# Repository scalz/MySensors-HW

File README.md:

# Mysensors HW
My personal Workspace for MySensors Hardware

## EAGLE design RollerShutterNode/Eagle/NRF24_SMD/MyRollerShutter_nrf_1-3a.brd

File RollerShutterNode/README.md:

# MyRollerShutter

This is a board for controlling rollershutters (0-100%) and detecting end stops with ACS712 for current sense of motor. 
It can control 3-wire motor only (Power, Up, Down wires), DC or AC, 12 to 230V. It's fine for me as I'm using AC motor. But this board can't work with 2wire DC motor.
You can connect 3 push buttons (UP/DOWN/STOP) and/or external i2c device (for tactile, gesture...). 

Of course, it can also be used as a relay board.

It is derived in two versions :

- NRF24 smd
- RFM69CW

I am using it with Mysensors lib. It's fun :)

### Important Note : I share this work for educational purpose. Be very careful with this. It's an AC Board which can be lethal. If you don't know what you are doing, I can't tell you enough to not do anything. 

### General 
------

|General spec.|  | 
|---|---|
|Size |44.4*45.4 (mm) |
| Components size | 0805 |
| MCU | Atmel328p TQFP |
| Radio | two versions : NRF24 smd or RFM69CW |
| Authentication security | ATSHA204A chip footprint |
| OverTheAir update | SPI flash eeprom footprint |
| Current Sensor | ACS712 5Amp current flow sensors footprint with  opamp signal condition. to have a nice 0-3V ADC curve |
| Relays | 2x 10Amp relays : OMRON G5Q type, 1xNO, 1xNO-NC for their footprint and quality|
| AC/DC Stepdown | HILINK_HLK-PM01 230V->5V |
| Screw terminals | 5mm pitch. Input AC, Motor Power Source, Motor Direction|
| Extension connectors | 3x JST 1mm pitch connectors : FTDI, AVRSPI, IOs | 

#### Onboard safety:

- Varistor 
- 5Amp fuse on AC Mains Input to handle relays. 
- 1Amp fuse for Hilink AC/DC Stepdown. 
- DS18B20A sensor for monitoring AC/DC step down temperature. 
- A dual relay driver to handle relays and parasite. 
- Milling slots for additional creepage.
- you can also : put some liquid tape on your AC pcb pads, and use an insulating box.

#### Extension Connectors description

- FTDI : JST 1mm pitch connector
- AVRSPI : JST 1mm pitch connector
- IOs : JST 1mm pitch connector -> 3V/GND/A4/A5/D3, for UP/DOWN/STOP buttons or I2C for external breakout (tactile switch, gesture...) or some shields I have designed :)

#### AC Connectors description
|Connector|  |
|---|---|
| Input AC | connect to AC line L to Live and N to Neutral |
| MotorPowerSource | for 12-24VDC just connect power source to 12_230 screwterminal, for 110-230V connect together the pins from Motor Power screwterminal |
|Motor Direction | Motor Up and Down lines |

#### Arduino Pin description
|Arduino sketch define| Arduino Pin | description |
|---|---|---|
| MY_OTA_FLASH_SS | 8 | EEprom CS pin |
| ATSHA204_PIN | 17/A3 | Arduino Digital I/O pin number for ATSHA204A sot23 ic (for authentication) |
| RELAY_UPDOWN  | 15/A1 | Digital I/O pin number for relay SPDT |
| RELAY_POWER | 16/A2 | Digital I/O pin number for relay SPST : Normally open, power off rollershutter motor, if A2==1 and A1==0 moveup, if A2==1 and A1==1 movedown, if A2==0 power off |
| DEBUG_LED |  6 | Digital I/O pin number for onboard debug led |
| BUTTON_STOP | 3 | Digital I/O pin number for button Stop |
| BUTTON_UP | 18/A4 | Digital I/O pin number for button Up or I2C |
| BUTTON_DOWN | 19/A5  | Digital I/O pin number for button Down or I2C |
| ACS712_SENSOR | A7 | ADC pin for ACS712 current sensor |
| DS18B20_PIN | 4 | One Wire Temperature sensor for onboard monitoring |

#### Q&A about my personal choice
##### Why not an ESP?
- I like these chips. But I don't want wifi for my rollershutter nodes. I prefer to use subghz radio+atsha signing ic.

##### Why current sensor for endstop detection?
- There are other option for just detecting a simple trigger, sure. I looked at it briefly, there was not a so big footprint saving, and I thought the current sensor would add more verstality to the board.

##### Why so much capa, using filtering for analog etc..
- some ferrites, caps etc. are not all mandatory. they help to improve things but without some parts it works well. It's there, in case, for debug, and still useful when there are some footprints available.

etc..

Finally :

- as each new thing I make, I enjoy the new challenge.
- I have tried to make a board dedicated for RollershutterNode with autocalibration, with as much features/options/versatility I could with the available footprint. 

#### About the ACS current sensor

ACS reading measurement results, from 0 to 1000W by 100W step :

For fun, this is the light bulbs I have used to do my measurements (5 lights bulbs can be powered separately, the other row in one time, so it's possible to do 100W steps)

For detail about opamp circuit see schematic.

### Example of use of this board : RollershutterNode 

#### How is the Rollershutter motor controlled:

On-board, there are 2x10Amp Relays. Rollershutter motor don't use 10Amp of course, nor 5Amp. May we expect no need of snubber, if using over rated relays? I hope :) If mandatory for you then, it should be external, not enough space onboard. That said, for a simple relay board too, you can control lot of thing with 10amp.

So, we have 2 relays, for the rollershutter:

- 1x NO  which enable/disable power on the second relay. It is like "Stop Motor".
- 1X NO-NC that you can toggle, and drive Up, or Down the rollershutter motor. Remember this relay needs to be enabled by the previous one.
    So relays are "interlocked", you can't enable "Up" and "Down" outputs to motor at same time and burn your motor.

#### How to open/close 0-100%

We need to detect the up and down endstops. It is managed by the onboard ACS7125 sensor. It will senses the motor current flow and we will read it with ADC on arduino. 
When motor is active, there is a power consumption. And when an up or down end is toggled, the motor stops (because of mechanical switch...). There is no power consumption. 

As you can see, with ACS712, we can know in which state we are. We are able to read some kind of power consuption curve too if needed and no mechanical ends switch available..
So, we need to know how long it takes to open the rollershutter, and to close (it may be not the exact timing open vs close time). 

#### Example sketch 

Note: the example sketch is for Mysensors v2.x. You can find it in example folder. It is state machine based, so no blocking loop. It's not very polished but it's working. I miss time, too much ideas&projects..I will look at it later. 

1. You just need to config your settings in the MyNodeDefinition.h
2. The ShutterSM.h and .cpp are the state machine for the shutter. You don't need to modify it, there are default settings.
3. State and settings of rollershutter are stored in eeprom.

The sketch present the following Mysensors CHILD_IDs, presented to a controller for instance :

| CHILD_ID | Description | 
|---|---|
| CHILD_ID_ROLLERSHUTTER | handle UP/DOWN/STOP/PERCENT |
| CHILD_ID_AUTOCALIBRATION | remotely start a calibration |
| CHILD_ID_TEMPERATURE | onboard temperature sensor, to monitor board&Hilink temperature |
| CHILD_ID_ENDSTOP | endstop. for debugging in case...Set it to simulate an endstop during calibration and tell the node that the shutter has reached the endstop (in case no mechanical switch etc..) |
| CHILD_ID_PERCENT | Rollershutter PERCENT for controller which are not Mysensors 2.0 compliant yet |
| CHILD_ID_CURRENT |Current sensor value, for debugging.. |

**At first launch**, the node will use the default values in the state machine and will know it's not calibrated. So, you can launch a calibration. That will automatically :

1. fully open the shutter.
2. fully close it and measure travel time.
3. fully open it and measure the travel time.
4. Done. Yeah! Parameters are stored in eeprom. 
5. If you push Up button, that will try to fully open. Down, Stop buttons will do their job too. The node store the new position in eeprom. From your controller, set a PERCENT and that will open as you want your shutter. so fun, so cool :)
etc..

### Overview

&nbsp; 

### Notes : 

### TODO

- 3d insulating case
- improve things. always improve :)

### Donations

I'm trying to make opensource projects. I do this for free and sharing spirit. I don't do ads etc..
But if you think information here is worth of some money, or want to reward me, feel free to send any amount through paypal.

Or you can also order pcb here :
I will earn a little percentage that will allow me to order proto pcb and share more fun design.

Or pay me a protein smoothie if you see me! oh well, a beer is ok too :)

### Contributors

Special thanks to:
- Mysensors Team for its great work
- Adafruit, sparkfun, TI, atmel etc.. for all educational infos they share

### Links, reference and license 

https://www.openhardware.io/view/22/Roller-Shutter-Node

Copyright Scalz (2016). released under the [CERN Open Hardware Licence v1.2](http://ohwr.org/cernohl)

This is an opensource hardware. So please respect at least license and do what you want with it ;)

Enjoy :)

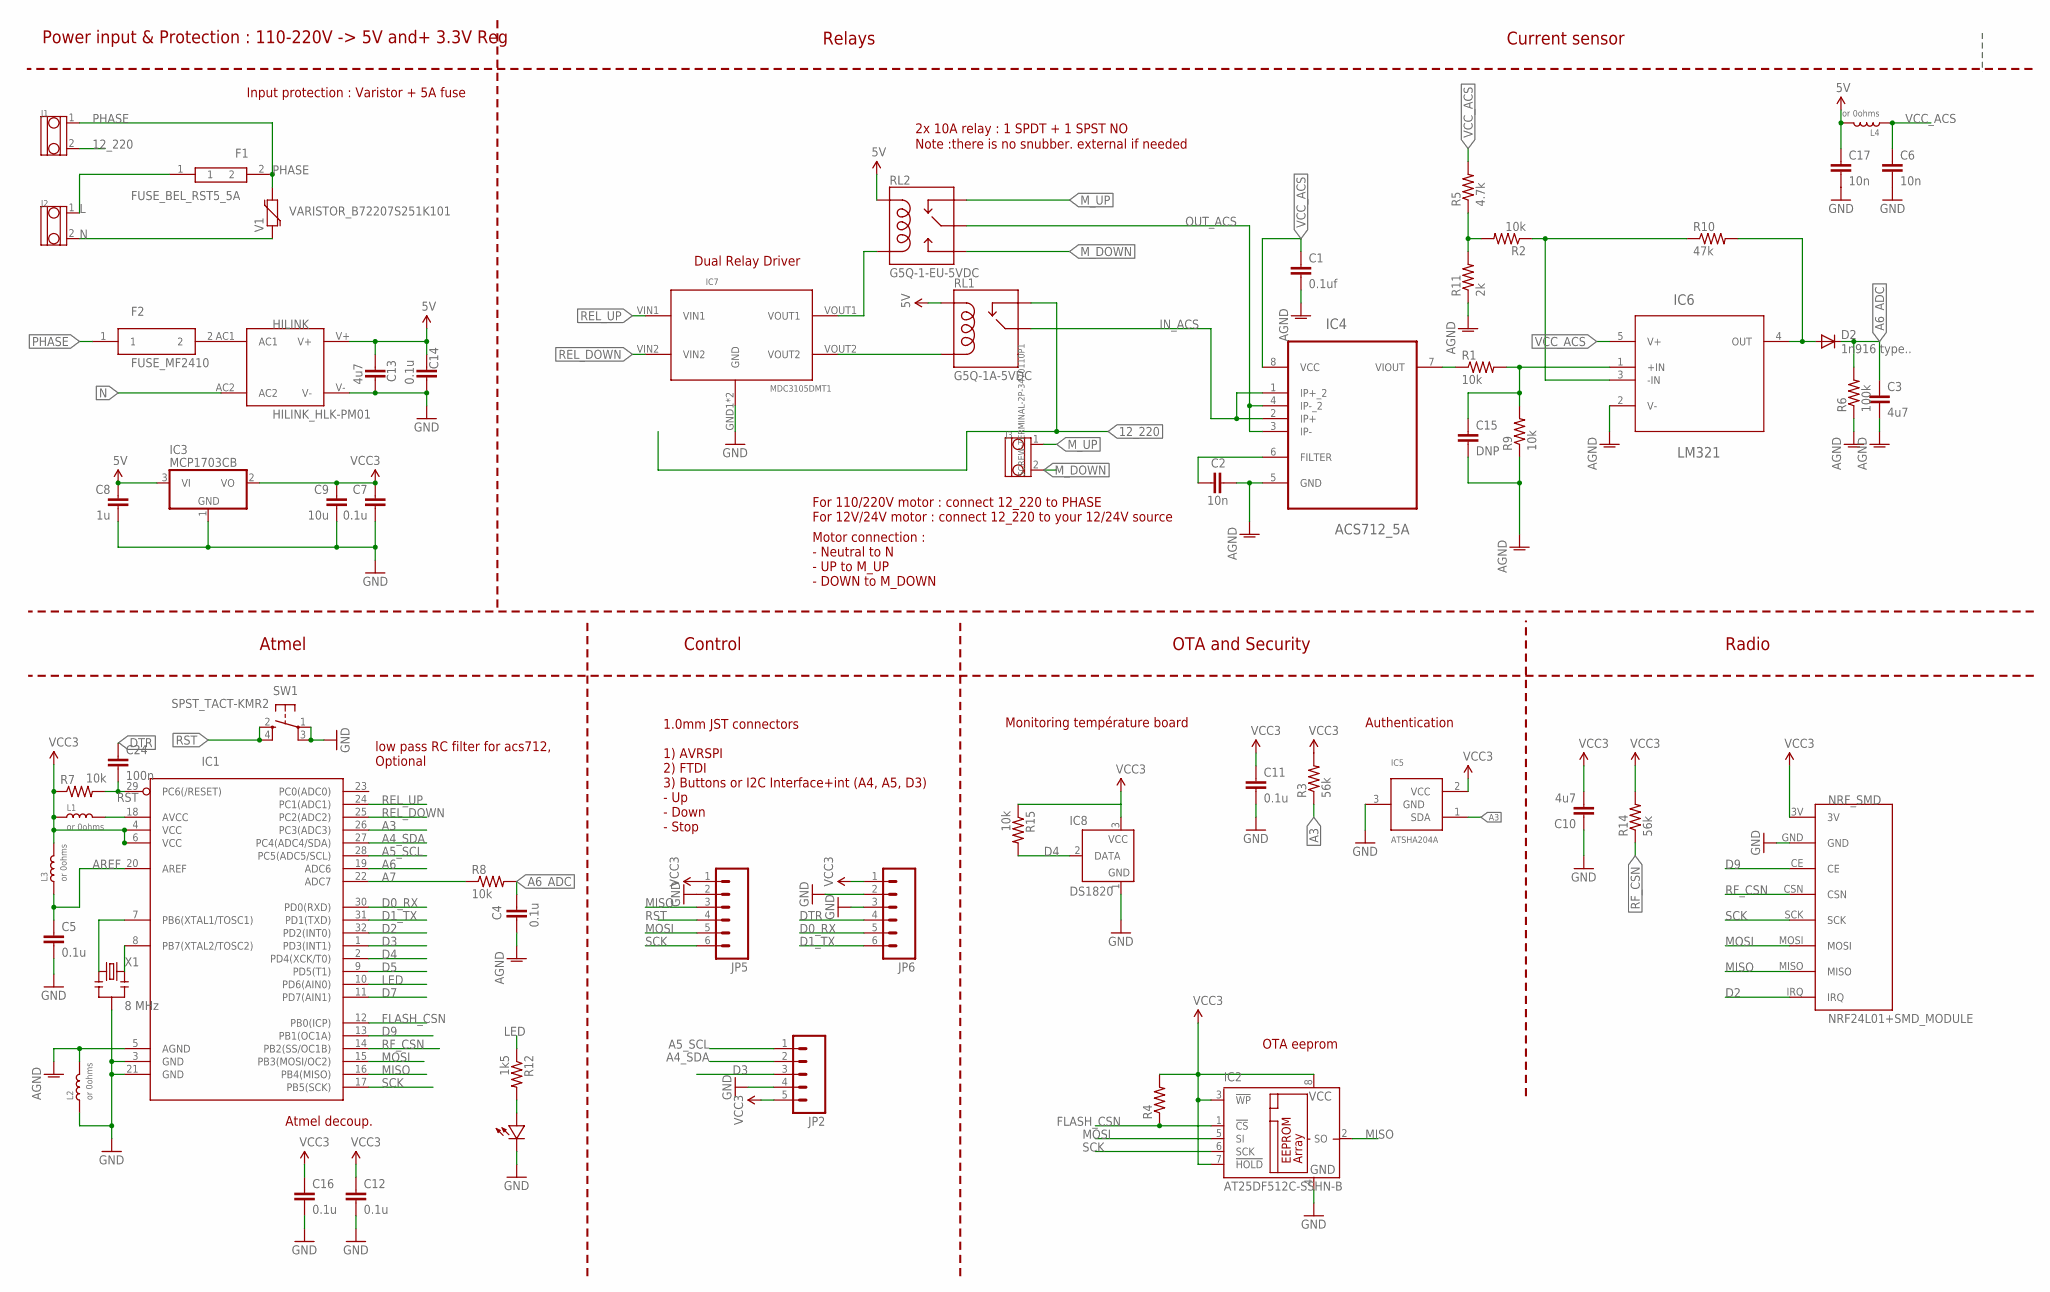
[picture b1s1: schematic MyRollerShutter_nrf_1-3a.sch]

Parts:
C1: 0.1uf; 0805-CAP
C2, C6, C17: 10n; 0805-CAP
C3, C10, C13: 4u7; 0805-CAP
C4, C5, C7, C11, C12, C14, C16: 0.1u; 0805-CAP
C8: 1u; 0805-CAP
C9: 10u; 0805-CAP
C15: DNP; 0805-CAP
C24: 100n; 0805-CAP
D1: LED0805; 0805-LED
D2: 1n916 type..; SOD-323
F1: FUSE_BEL_RST5_5A
F2: FUSE_MF2410; 2410
HILINK: HILINK_HLK-PM01
IC1: ATMega-328; TQFP32-08
IC2: AT25DF512C-SSHN-B; SO-08
IC3: MCP1703CB; SOT23
IC4: ACS712_5A; SOIC127P600X175-8N
IC5: ATSHA204A; SOT23
IC6: LM321; SOT95P285X120-5N
IC7: MDC3105DMT1
IC8: DS1820; TO92-
J1, J2, J3: SCREW-TERMINAL-2P-3470110P1; 2P-5.0
JP2: M05SMD; 1X05-1MM
JP5, JP6: M06SMD-1MM; 1X06-1MM
L1, L2, L3, L4: or 0ohms; L0805
NRF_SMD: NRF24L01+SMD_MODULE
R1, R2, R7, R8, R9, R15: 10k; 0805-RES
R3, R14: 56k; 0805-RES
R4: RESISTOR0805-RES; 0805-RES
R5: 4.7k; 0805-RES
R6: 100k; 0805-RES
R10: 47k; 0805-RES
R11: 2k; 0805-RES
R12: 1k5; 0805-RES
RL1: G5Q-1A-5VDC; G5Q_SINGLE
RL2: G5Q-1-EU-5VDC; RELAY-G5Q
SW1: SPST_TACT-KMR2; KMR2
V1: VARISTOR_B72207S251K101
X1: 8 MHz; RESONATOR-SMD

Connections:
5V: C8.1, C13.1, C14.1, C17.1, HILINK.V+, IC3.3 (VI), L4.2, RL1.1 (COIL1), RL2.5 (COIL1)
12_220: J1.2, RL1.3 (NC)
A3: IC1.26 (PC3(ADC3)), IC5.1 (SDA), R3.1
A4_SDA: IC1.27 (PC4(ADC4/SDA)), JP2.2
A5_SCL: IC1.28 (PC5(ADC5/SCL)), JP2.1
A6: IC1.19 (ADC6)
A6_ADC: C3.1, C4.2, D2.1 (C), R6.2, R8.2
A7: IC1.22 (ADC7), R8.1
AGND: C1.2, C2.2, C3.2, C4.1, C15.2, IC1.5 (AGND), IC4.5 (GND), IC6.2 (V-), L2.2, R6.1, R9.1, R11.1
AREF: C5.1, IC1.20 (AREF), L3.1
D0_RX: IC1.30 (PD0(RXD)), JP6.5
D1_TX: IC1.31 (PD1(TXD)), JP6.6
D2: IC1.32 (PD2(INT0)), NRF_SMD.IRQ
D3: IC1.1 (PD3(INT1)), JP2.3
D4: IC1.2 (PD4(XCK/T0)), IC8.2 (DATA), R15.2
D5: IC1.9 (PD5(T1))
D7: IC1.11 (PD7(AIN1))
D9: IC1.13 (PB1(OC1A)), NRF_SMD.CE
DTR: C24.1, JP6.4
FLASH_CSN: IC1.12 (PB0(ICP)), IC2.1 (!CS), R4.1
GND: C5.2, C6.2, C7.2, C8.2, C9.2, C10.1, C11.2, C12.2, C13.2, C14.2, C16.2, C17.2, D1.MINUS, HILINK.V-, IC1.3 (GND), IC1.21 (GND), IC2.4 (GND), IC3.1 (GND), IC5.3 (GND), IC7.GND1 (GND), IC7.GND2 (GND), IC8.1 (GND), JP2.4, JP5.2, JP6.2, JP6.3, L2.1, NRF_SMD.GND, SW1.1, SW1.3 (P1), X1.2
IN_ACS: IC4.1 (IP+_2), IC4.2 (IP+), RL1.2 (MAIN)
L: F1.1, J2.1
LED: IC1.10 (PD6(AIN0)), R12.1
LM_OUT: D2.2 (A), IC6.4 (OUT), R10.2
MISO: IC1.16 (PB4(MISO)), IC2.2 (SO), JP5.3, NRF_SMD.MISO
MOSI: IC1.15 (PB3(MOSI/OC2)), IC2.5 (SI), JP5.5, NRF_SMD.MOSI
M_DOWN: J3.2, RL2.3 (NO)
M_UP: J3.1, RL2.4 (NC)
N: HILINK.AC2, J2.2, V1.1
unnamed: C2.1, IC4.6 (FILTER)
unnamed: IC4.7 (VIOUT), R1.1
unnamed: IC1.18 (AVCC), L1.2
unnamed: IC7.VOUT2, RL1.5 (COIL2)
unnamed: F2.2, HILINK.AC1
unnamed: C15.1, IC6.1 (+IN), R1.2, R9.2
unnamed: IC6.3 (-IN), R2.1, R10.1
unnamed: IC1.7 (PB6(XTAL1/TOSC1)), X1.1
unnamed: D1.PLUS, R12.2
unnamed: R2.2, R5.1, R11.2
unnamed: IC7.VOUT1, RL2.1 (COIL2)
unnamed: IC1.8 (PB7(XTAL2/TOSC2)), X1.3
OUT_ACS: IC4.3 (IP-), IC4.4 (IP-_2), RL2.2 (MAIN)
PHASE: F1.2, F2.1, J1.1, V1.2
REL_DOWN: IC1.25 (PC2(ADC2)), IC7.VIN2
REL_UP: IC1.24 (PC1(ADC1)), IC7.VIN1
RF_CSN: IC1.14 (PB2(SS/OC1B)), NRF_SMD.CSN, R14.1
RST: C24.2, IC1.29 (PC6(/RESET)), JP5.4, R7.2, SW1.2 (S), SW1.4 (S1)
SCK: IC1.17 (PB5(SCK)), IC2.6 (SCK), JP5.6, NRF_SMD.SCK
VCC: C7.1, C9.1, C10.2, C11.1, C12.1, C16.1, IC1.4 (VCC), IC1.6 (VCC), IC2.3 (!WP), IC2.7 (!HOLD), IC2.8 (VCC), IC3.2 (VO), IC5.2 (VCC), IC8.3 (VCC), JP2.5, JP5.1, JP6.1, L1.1, L3.2, NRF_SMD.3V, R3.2, R4.2, R7.1, R14.2, R15.1
VCC_ACS: C1.1, C6.1, IC4.8 (VCC), IC6.5 (V+), L4.1, R5.2

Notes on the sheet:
Authentication
Control
1.0mm JST connectors 1) AVRSPI 2) FTDI 3) Buttons or I2C Interface+int (A4, A5, D3) - Up - Down - Stop
Input protection : Varistor + 5A fuse
Dual Relay Driver
Power input & Protection : 110-220V -> 5V and+ 3.3V Reg
Relays
Current sensor
OTA and Security
Radio
Atmel
low pass RC filter for acs712, Optional
Note :there is no snubber. external if needed
Atmel decoup.
2x 10A relay : 1 SPDT + 1 SPST NO
Monitoring température board
For 110/220V motor : connect 12_220 to PHASE For 12V/24V motor : connect 12_220 to your 12/24V source
Motor connection : - Neutral to N - UP to M_UP - DOWN to M_DOWN
OTA eeprom

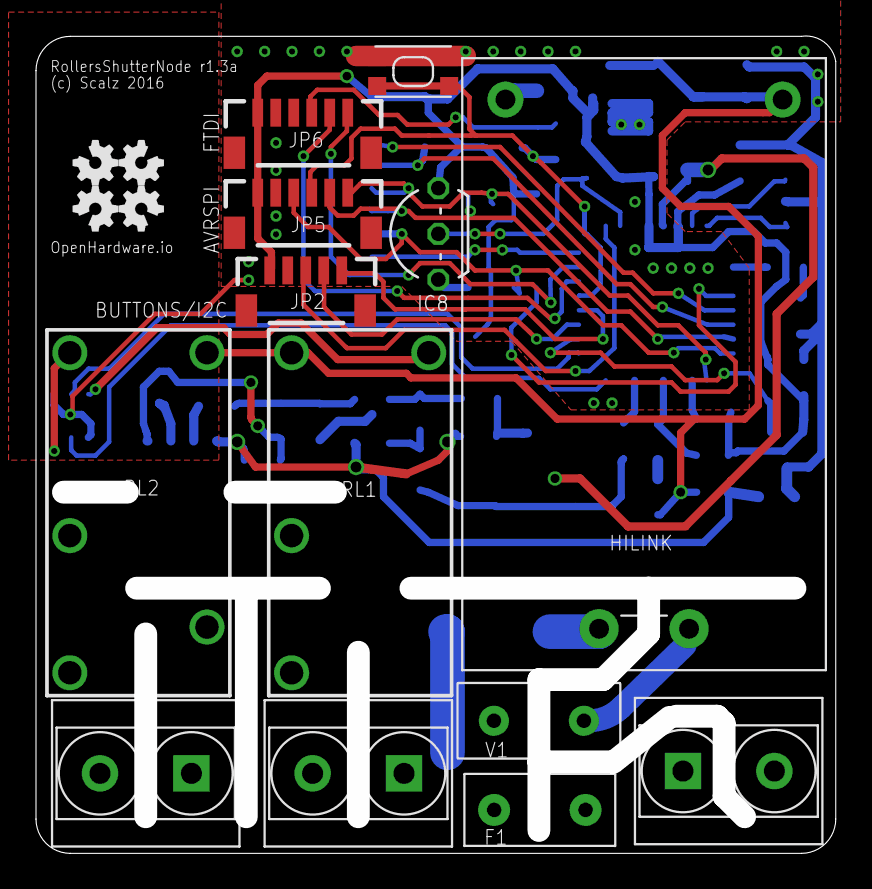
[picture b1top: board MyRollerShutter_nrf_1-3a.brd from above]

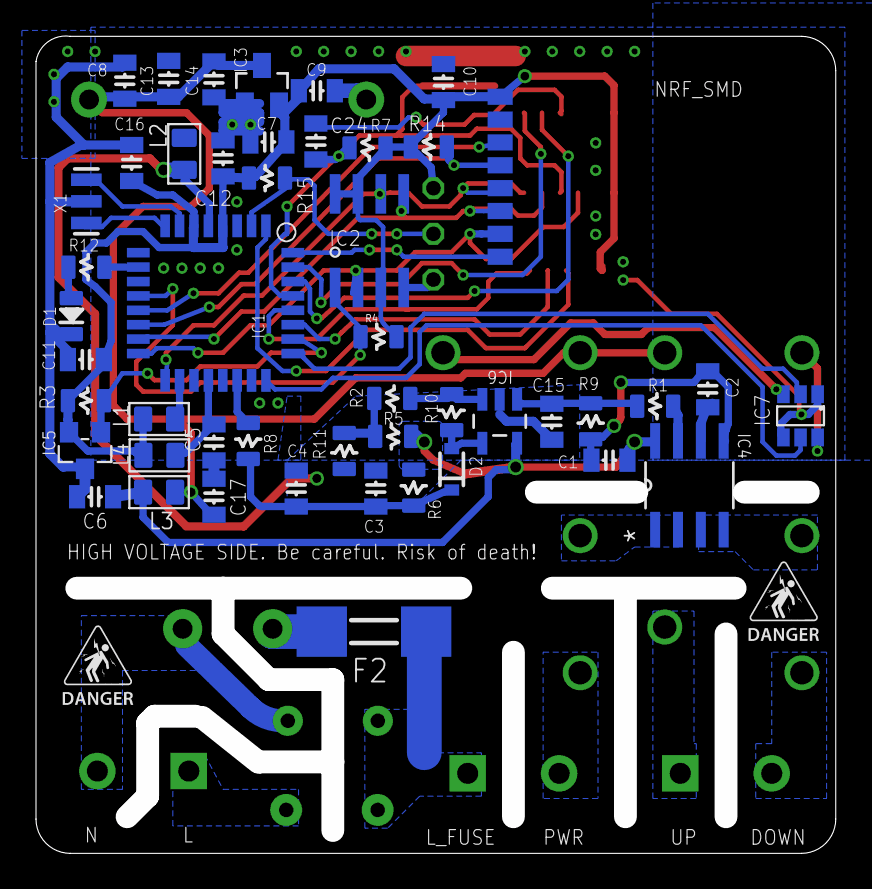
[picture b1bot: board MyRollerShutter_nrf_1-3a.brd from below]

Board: 2 copper layers, 44.4 x 45.4 mm, 64 parts (50 on the bottom side), 48 nets.

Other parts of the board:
U$2, U$3: ELECTROCUTION_SMALL
U$5: OPENHW_IO_SMALL

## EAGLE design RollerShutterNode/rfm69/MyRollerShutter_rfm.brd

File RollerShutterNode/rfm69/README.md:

# RollerShutterNode (RFM69 version)

It is a board for controlling rollershutter (0-100%) and detecting end stops with ACS712 for current sense of motor. It can be used as a relay board too.
You can connect 3 push buttons (UP/DOWN/STOP) and/or external i2c device (for tactile, gesture...). 
It can control 12-220V motors.

It is derived in two versions : 
- NRF24 smd
- RFM69(H)W

I will use it with Mysensors lib.

Size : 47x48 (mm)
Components size 0805.

###Important Note : I share this work for educational purpose. Be very careful with this. It's an AC Board which can be lethal. If you don't know what you are doing, I can't tell you enough to not do anything. 

####General spec
- Atmel328p TQFP
- NRF24 smd or RFM69(H)W footprint
- ATSHA204A authentication footprint
- eeprom footprint for OTA
- ACS712 5Amp footprint
- 2x 10Amp relays : 1xNO G5Q-1A-5VDC and 1xNO-NC G5Q-1-EU-5VDC driven by dual relay driver
- AC/DC Stepdown 220V-5V : HILINK_HLK-PM01 protected by varistor & fuse
- 5mm pitch screw terminals
- I2C connector for optional tactile sensor chip

####Arduino Pin description
- A0 : ADC ACS712
- A3 : ATSHA204A data
- A2 : Down Relay
- A1 : Up relay
- I2C connector : SDA, SCL, D3, D4
- A7 : CTN thermistor to check temperature under Hilink Stepdown

####Connectors 
- FTDI for bootloading
- AVRSPI for programming Atmel328p
- D3 : optional IO
- D4 : optional IO
- D6 : Up button
- D7 : Down button
- D5 : Stop button
- gnd

####AC Connector description
- N : Neutral (Neutre)
- L : Live (Phase)
- 12_220 : optional. If using 220v motor, you need to tie it with Source on Motor Connector

####Motor Connector description
- Up : Motor Up 
- Down : Motor Down
- Source : 12-24v motor source. If using 220v motor, tie it with 12_220 on AC Connector

### Board overview  

&nbsp; 

####Notes : 
- removed gerbers as it is still in dev and it's an AC board which can be lethal if not well used..

####TODO 
- sketch for rollershutter (buttons, calibration functions, controlling 0-100%...). 
- reduce board size

Note : it is still in dev. 

####Links, reference and license 
Copyright scalz (2015). released under the [CERN Open Hardware Licence v1.2](http://ohwr.org/cernohl)

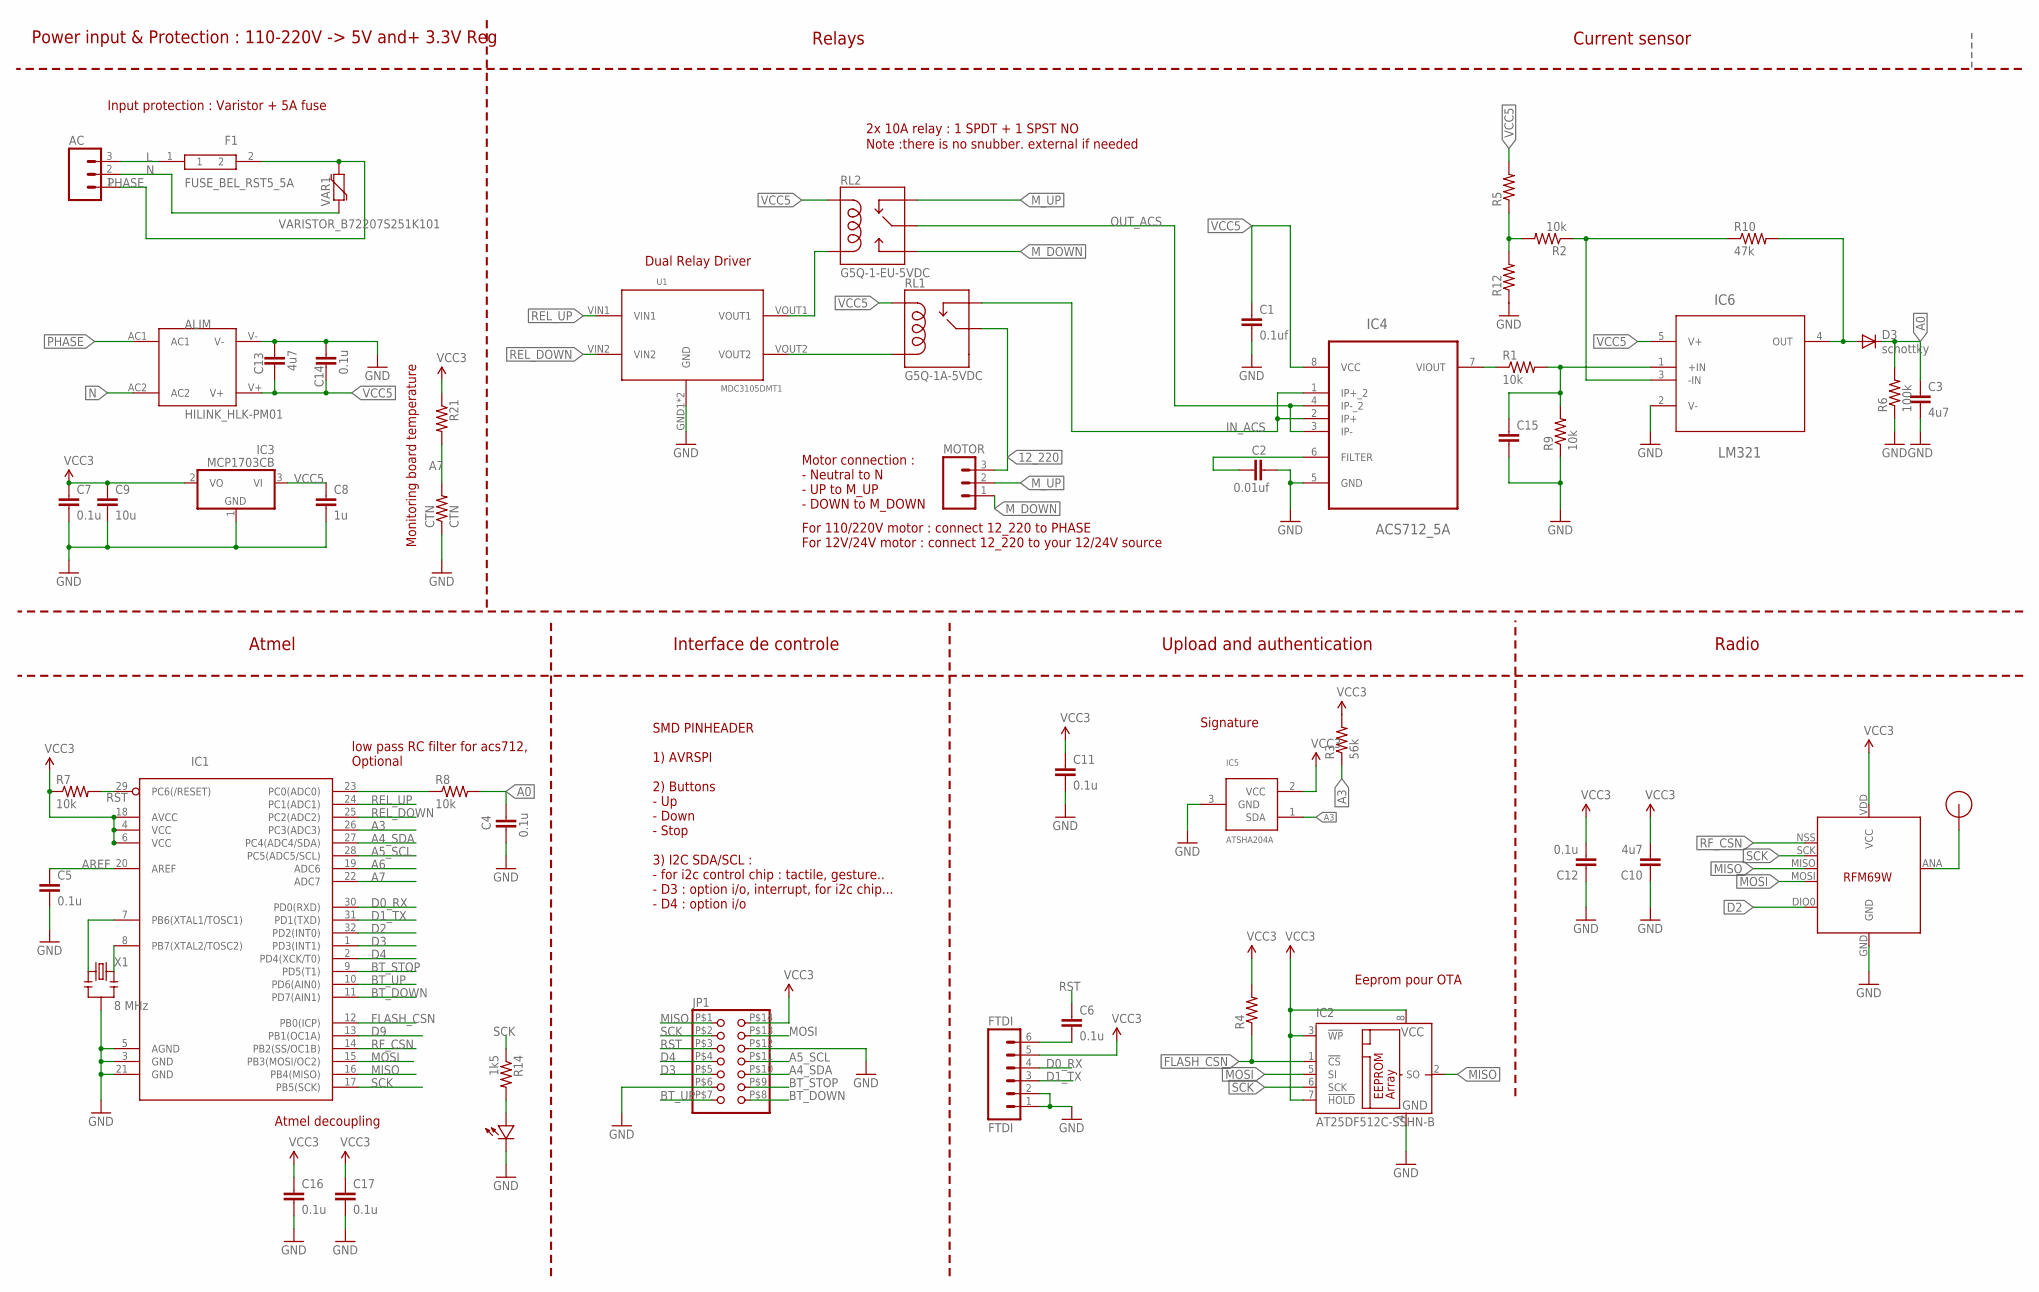
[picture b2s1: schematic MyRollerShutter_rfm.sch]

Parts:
AC: M03-SCREW-5MM; SCREWTERMINAL-5MM-3
ALIM: HILINK_HLK-PM01
ANT: RFM12B_ANTENNA; RFM12B-ANTENNA
C1: 0.1uf; 0805-CAP
C2: 0.01uf; 0805-CAP
C3, C10, C13: 4u7; 0805-CAP
C4, C5, C6, C7, C11, C12, C14, C16, C17: 0.1u; 0805-CAP
C8: 1u; 0805-CAP
C9: 10u; 0805-CAP
C15: CAP0805-CAP; 0805-CAP
CTN: CTN; 0805-RES
D3: schottky; SOD-323
D4: LED0805; 0805-LED
F1: FUSE_BEL_RST5_5A
FTDI: FTDI; 1X06
IC1: ATMega-328; TQFP32-08
IC2: AT25DF512C-SSHN-B; SO-08
IC3: MCP1703CB; SOT23
IC4: ACS712_5A; SOIC127P600X175-8N
IC5: ATSHA204A; SOT23
IC6: LM321; SOT95P285X120-5N
JP1: PINHD-2X7; 2X07
MOTOR: M03-SCREW-5MM; SCREWTERMINAL-5MM-3
R1, R2, R7, R8, R9: 10k; 0805-RES
R3: 56k; 0805-RES
R4, R5, R12, R21: RESISTOR0805-RES; 0805-RES
R6: 100k; 0805-RES
R10: 47k; 0805-RES
R14: 1k5; 0805-RES
RFM69: RFM69; RFM69W-MINPADS
RL1: G5Q-1A-5VDC; G5Q_SINGLE
RL2: G5Q-1-EU-5VDC; RELAY-G5Q
U1: MDC3105DMT1
VAR1: VARISTOR_B72207S251K101
X1: 8 MHz; RESONATOR-SMD

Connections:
12_220: MOTOR.3, RL1.2 (MAIN)
A0: C3.1, C4.2, D3.1 (C), R6.2, R8.2
A3: IC1.26 (PC3(ADC3)), IC5.1 (SDA), R3.1
A4_SDA: IC1.27 (PC4(ADC4/SDA)), JP1.P$10 (10)
A5_SCL: IC1.28 (PC5(ADC5/SCL)), JP1.P$11 (8)
A6: IC1.19 (ADC6)
A7: CTN.2, IC1.22 (ADC7), R21.2
AREF: C5.1, IC1.20 (AREF)
BT_DOWN: IC1.11 (PD7(AIN1)), JP1.P$8 (14)
BT_STOP: IC1.9 (PD5(T1)), JP1.P$9 (12)
BT_UP: IC1.10 (PD6(AIN0)), JP1.P$7 (13)
D0_RX: FTDI.4, IC1.30 (PD0(RXD))
D1_TX: FTDI.3, IC1.31 (PD1(TXD))
D2: IC1.32 (PD2(INT0)), RFM69.DIO0
D3: IC1.1 (PD3(INT1)), JP1.P$5 (9)
D4: IC1.2 (PD4(XCK/T0)), JP1.P$4 (7)
D9: IC1.13 (PB1(OC1A))
FLASH_CSN: IC1.12 (PB0(ICP)), IC2.1 (!CS), R4.1
GND: ALIM.V-, C1.2, C2.2, C3.2, C4.1, C5.2, C7.2, C8.2, C9.2, C10.1, C11.2, C12.1, C13.2, C14.2, C15.2, C16.2, C17.2, CTN.1, D4.MINUS, FTDI.1, FTDI.2, IC1.3 (GND), IC1.5 (AGND), IC1.21 (GND), IC2.4 (GND), IC3.1 (GND), IC4.5 (GND), IC5.3 (GND), IC6.2 (V-), JP1.P$6 (11), JP1.P$12 (6), R6.1, R9.1, R12.1, RFM69.GND, U1.GND1 (GND), U1.GND2 (GND), X1.2
IN_ACS: IC4.1 (IP+_2), IC4.2 (IP+), RL1.3 (NC)
L: AC.3, F1.1
LM_OUT: D3.2 (A), IC6.4 (OUT), R10.2
MISO: IC1.16 (PB4(MISO)), IC2.2 (SO), JP1.P$1 (1), RFM69.MISO
MOSI: IC1.15 (PB3(MOSI/OC2)), IC2.5 (SI), JP1.P$13 (4), RFM69.MOSI
M_DOWN: MOTOR.1, RL2.3 (NO)
M_UP: MOTOR.2, RL2.4 (NC)
N: AC.2, ALIM.AC2, VAR1.1
unnamed: C2.1, IC4.6 (FILTER)
unnamed: IC4.7 (VIOUT), R1.1
unnamed: ANT.P$1, RFM69.ANA (ANT)
unnamed: RL1.5 (COIL2), U1.VOUT2
unnamed: C15.1, IC6.1 (+IN), R1.2, R9.2
unnamed: IC6.3 (-IN), R2.1, R10.1
unnamed: IC1.7 (PB6(XTAL1/TOSC1)), X1.1
unnamed: IC1.23 (PC0(ADC0)), R8.1
unnamed: D4.PLUS, R14.2
unnamed: R2.2, R5.1, R12.2
unnamed: RL2.1 (COIL2), U1.VOUT1
unnamed: C6.2, FTDI.6
unnamed: IC1.8 (PB7(XTAL2/TOSC2)), X1.3
OUT_ACS: IC4.3 (IP-), IC4.4 (IP-_2), RL2.2 (MAIN)
PHASE: AC.1, ALIM.AC1, F1.2, VAR1.2
REL_DOWN: IC1.25 (PC2(ADC2)), U1.VIN2
REL_UP: IC1.24 (PC1(ADC1)), U1.VIN1
RF_CSN: IC1.14 (PB2(SS/OC1B)), RFM69.NSS (SEL)
RST: C6.1, IC1.29 (PC6(/RESET)), JP1.P$3 (5), R7.2
SCK: IC1.17 (PB5(SCK)), IC2.6 (SCK), JP1.P$2 (3), R14.1, RFM69.SCK
VCC: C7.1, C9.1, C10.2, C11.1, C12.2, C16.1, C17.1, FTDI.5, IC1.4 (VCC), IC1.6 (VCC), IC1.18 (AVCC), IC2.3 (!WP), IC2.7 (!HOLD), IC2.8 (VCC), IC3.2 (VO), IC5.2 (VCC), JP1.P$14 (2), R3.2, R4.2, R7.1, R21.1, RFM69.VDD (VCC)
VCC5: ALIM.V+, C1.1, C8.1, C13.1, C14.1, IC3.3 (VI), IC4.8 (VCC), IC6.5 (V+), R5.2, RL1.1 (COIL1), RL2.5 (COIL1)

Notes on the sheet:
Eeprom pour OTA
Signature
Interface de controle
Input protection : Varistor + 5A fuse
Dual Relay Driver
Power input & Protection : 110-220V -> 5V and+ 3.3V Reg
Relays
Current sensor
Upload and authentication
Radio
Atmel
Atmel decoupling
2x 10A relay : 1 SPDT + 1 SPST NO
Monitoring board temperature
For 110/220V motor : connect 12_220 to PHASE For 12V/24V motor : connect 12_220 to your 12/24V source
Motor connection : - Neutral to N - UP to M_UP - DOWN to M_DOWN
Note :there is no snubber. external if needed
SMD PINHEADER 1) AVRSPI 2) Buttons - Up - Down - Stop 3) I2C SDA/SCL : - for i2c control chip : tactile, gesture.. - D3 : option i/o, interrupt, for i2c chip... - D4 : option i/o
low pass RC filter for acs712, Optional

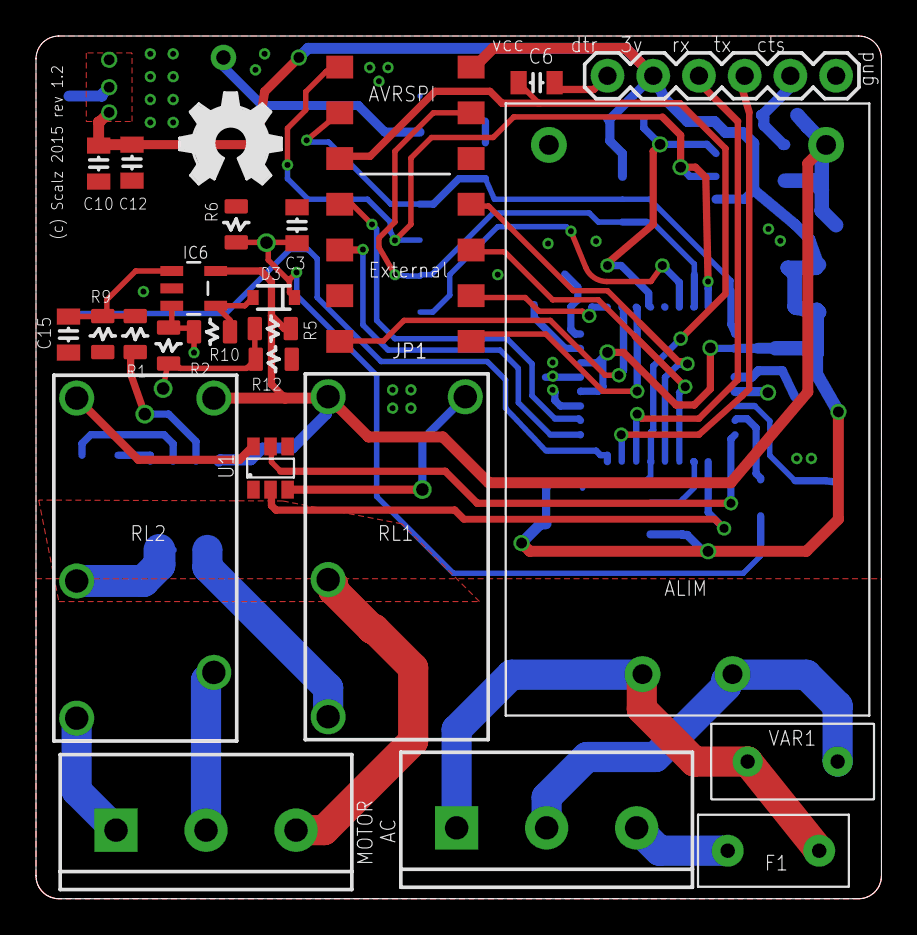
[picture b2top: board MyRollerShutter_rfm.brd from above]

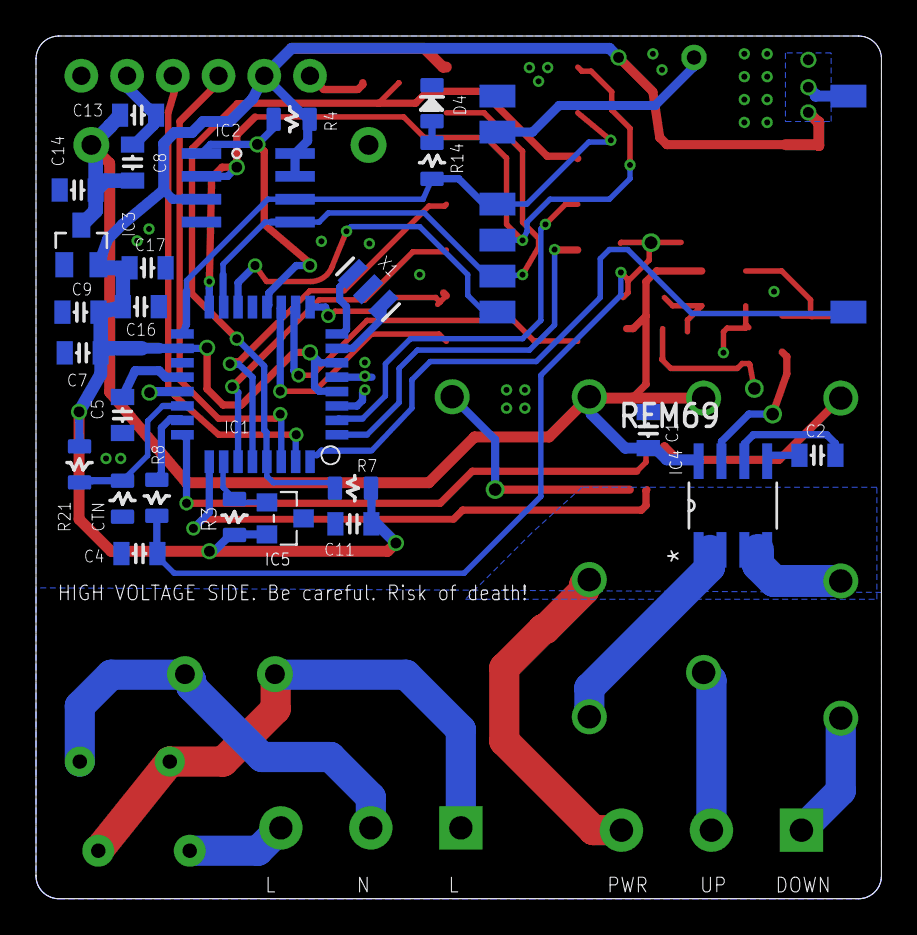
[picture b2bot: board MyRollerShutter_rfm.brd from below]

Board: 2 copper layers, 47.0 x 47.9 mm, 53 parts (27 on the bottom side), 47 nets.

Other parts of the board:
U$4: OSHW_FILLX200_NOTEXT

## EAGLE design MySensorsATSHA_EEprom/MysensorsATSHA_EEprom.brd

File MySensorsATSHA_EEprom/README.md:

# MysensorsATSHA_EEprom

A simple breadboard with :
- ATSHA204A SOT23 authentication footprint (ATSHA204A-STUCZ-T)
- Eeprom for OTA (AT25DF512C-SSHN-B)

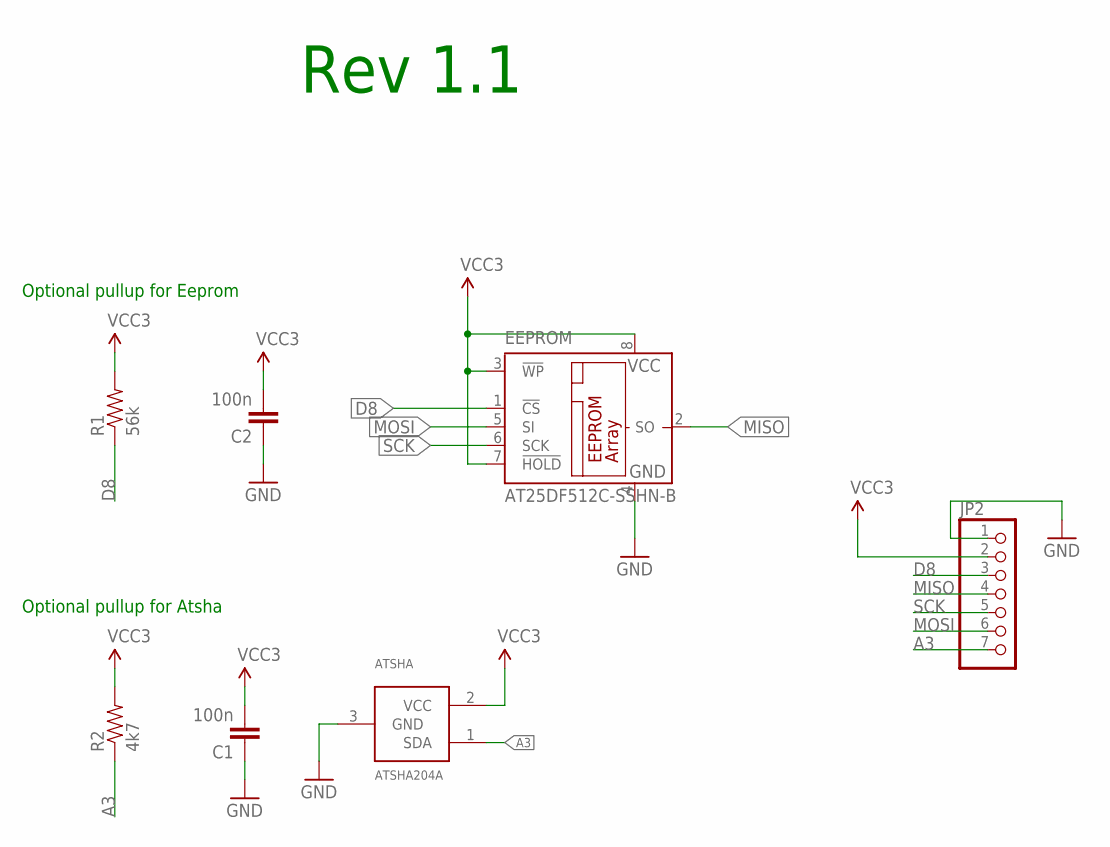
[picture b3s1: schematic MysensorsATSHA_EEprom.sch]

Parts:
ATSHA: ATSHA204A; SOT23
C1, C2: 100n; 1206
EEPROM: AT25DF512C-SSHN-B; SO-08
JP2: PINHD-1X7; 1X07
R1: 56k; 1206
R2: 4k7; 1206

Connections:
A3: ATSHA.1 (SDA), JP2.7, R2.1
D8: EEPROM.1 (!CS), JP2.3, R1.1
GND: ATSHA.3 (GND), C1.1, C2.1, EEPROM.4 (GND), JP2.1
MISO: EEPROM.2 (SO), JP2.4
MOSI: EEPROM.5 (SI), JP2.6
SCK: EEPROM.6 (SCK), JP2.5
VCC: ATSHA.2 (VCC), C1.2, C2.2, EEPROM.3 (!WP), EEPROM.7 (!HOLD), EEPROM.8 (VCC), JP2.2, R1.2, R2.2

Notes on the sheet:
Optional pullup for Eeprom
Optional pullup for Atsha
Rev 1.1

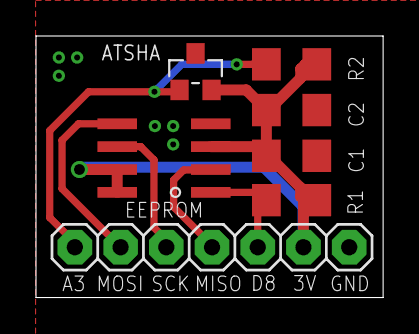
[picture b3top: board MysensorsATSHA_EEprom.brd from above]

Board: 2 copper layers, 19.3 x 14.5 mm, 7 parts (0 on the bottom side), 7 nets.

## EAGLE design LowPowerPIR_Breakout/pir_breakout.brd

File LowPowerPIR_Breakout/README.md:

# Low Power PIR Breakout

Note: Deprecated, I will update it soon.

It is a small, slim, low power PIR Breakout board for evaluation on breadboard, or it can be integrated in small enclosure.

It is based on TI AN4368. Changes I made are :
- 2x potentiometer added
- debug points
- optional led on Out Signal (for debug)

Size : 24x19.7 (mm)
Components size 0805.

#### Pinout :
- VCC. Note : As it is designed for low power operation, it is not regulated. So 3.3V max.
- OUT : trigger signal output
- GND

### Board overview  

&nbsp; 

3d Preview : https://www.youtube.com/watch?v=Lc4ZXmKnMNw

Board can be ordered here : https://oshpark.com/shared_projects/Dc6Tlrt1

####TODO : 
-  -> oscilloscope testings..

Note : I am waiting for pcbs so it is still in dev

####Links, reference and license : 

Copyright scalz (2015). released under the [CERN Open Hardware Licence v1.2](http://ohwr.org/cernohl)

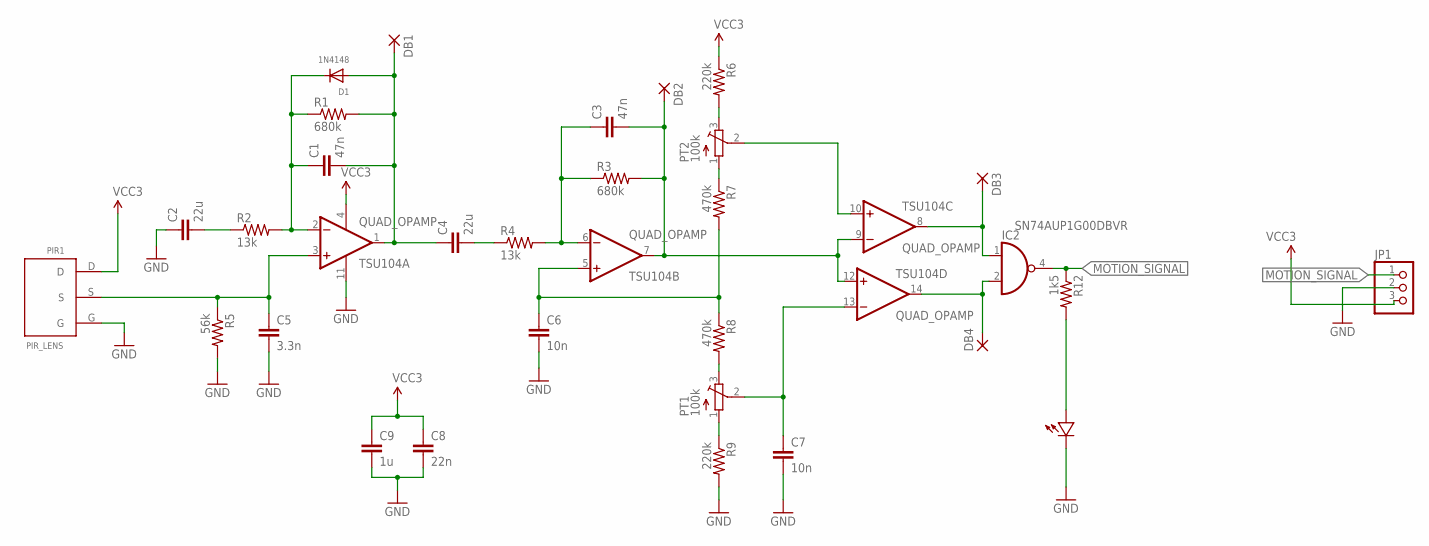
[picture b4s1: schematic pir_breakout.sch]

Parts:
C1, C3: 47n; 0805-CAP
C2, C4: 22u; 0805-CAP
C5: 3.3n; 0805-CAP
C6, C7: 10n; 0805-CAP
C8: 22n; 0805-CAP
C9: 1u; 0805-CAP
D1: 1N4148; SOD-123
D2: LED0805; 0805-LED
DB1, DB2, DB3, DB4: 1,6/0,8
IC2: SN74AUP1G00DBVR; SOT23-5
JP1: PINHD-1X3; 1X03
PIR1: PIR_LENS
PT1, PT2: 100k; TC33X
R1, R3: 680k; 0805-RES
R2, R4: 13k; 0805-RES
R5: 56k; 0805-RES
R6, R9: 220k; 0805-RES
R7, R8: 470k; 0805-RES
R12: 1k5; 0805-RES
TSU104: QUAD_OPAMP; TSSOP-14

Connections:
GND: C2.1, C5.2, C6.2, C7.2, C8.2, C9.2, D2.MINUS, IC2.3 (GND), JP1.2, PIR1.G, R5.2, R9.2, TSU104.11 (V-)
MOTION_SIGNAL: IC2.4 (O), JP1.1, R12.1
unnamed: C7.1, PT1.2 (S), TSU104.13 (-IN)
unnamed: PT1.1 (A), R9.1
unnamed: C5.1, PIR1.S, R5.1, TSU104.3 (+IN)
unnamed: PT1.3 (E), R8.2
unnamed: C1.1, D1.C, R1.1, R2.2, TSU104.2 (-IN)
unnamed: C2.2, R2.1
unnamed: C1.2, C4.1, D1.A, DB1.1, R1.2, TSU104.1 (OUT)
unnamed: C4.2, R4.1
unnamed: C3.1, R3.1, R4.2, TSU104.6 (-IN)
unnamed: C3.2, DB2.1, R3.2, TSU104.7 (OUT), TSU104.9 (-IN), TSU104.12 (+IN)
unnamed: DB3.1, IC2.1 (I0), TSU104.8 (OUT)
unnamed: DB4.1, IC2.2 (I1), TSU104.14 (OUT)
unnamed: PT2.2 (S), TSU104.10 (+IN)
unnamed: PT2.3 (E), R6.2
unnamed: PT2.1 (A), R7.1
unnamed: D2.PLUS, R12.2
unnamed: C6.1, R7.2, R8.1, TSU104.5 (+IN)
VCC: C8.1, C9.1, IC2.5 (VCC), JP1.3, PIR1.D, R6.1, TSU104.4 (V+)

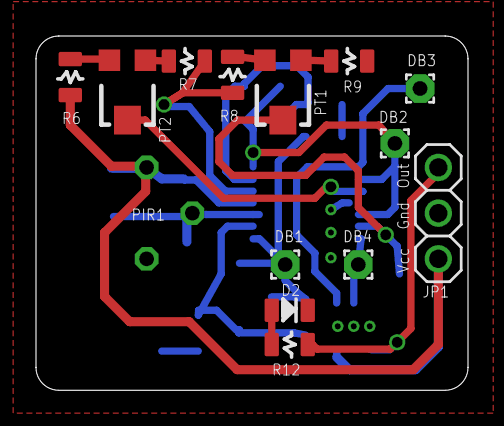
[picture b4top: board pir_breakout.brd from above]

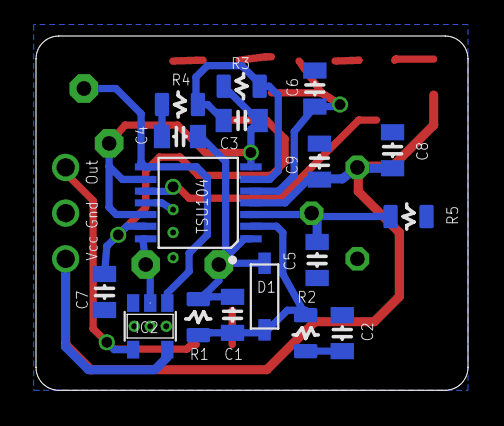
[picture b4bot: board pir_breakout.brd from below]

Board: 2 copper layers, 24.0 x 19.7 mm, 31 parts (17 on the bottom side), 20 nets.

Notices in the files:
RollerShutterNode/README.md:
https://www.openhardware.io/view/22/Roller-Shutter-Node
Copyright Scalz (2016). released under the [CERN Open Hardware Licence v1.2](http://ohwr.org/cernohl)
This is an opensource hardware. So please respect at least license and do what you want with it ;)
Enjoy :)
parts and their libraries:
SparkFun-Aesthetics: Licensing: Creative Commons ShareAlike 4.0 International - https://creativecommons.org/licenses/by-sa/4.0
pmo_lib: CC-BY-NC-SA 4.0
